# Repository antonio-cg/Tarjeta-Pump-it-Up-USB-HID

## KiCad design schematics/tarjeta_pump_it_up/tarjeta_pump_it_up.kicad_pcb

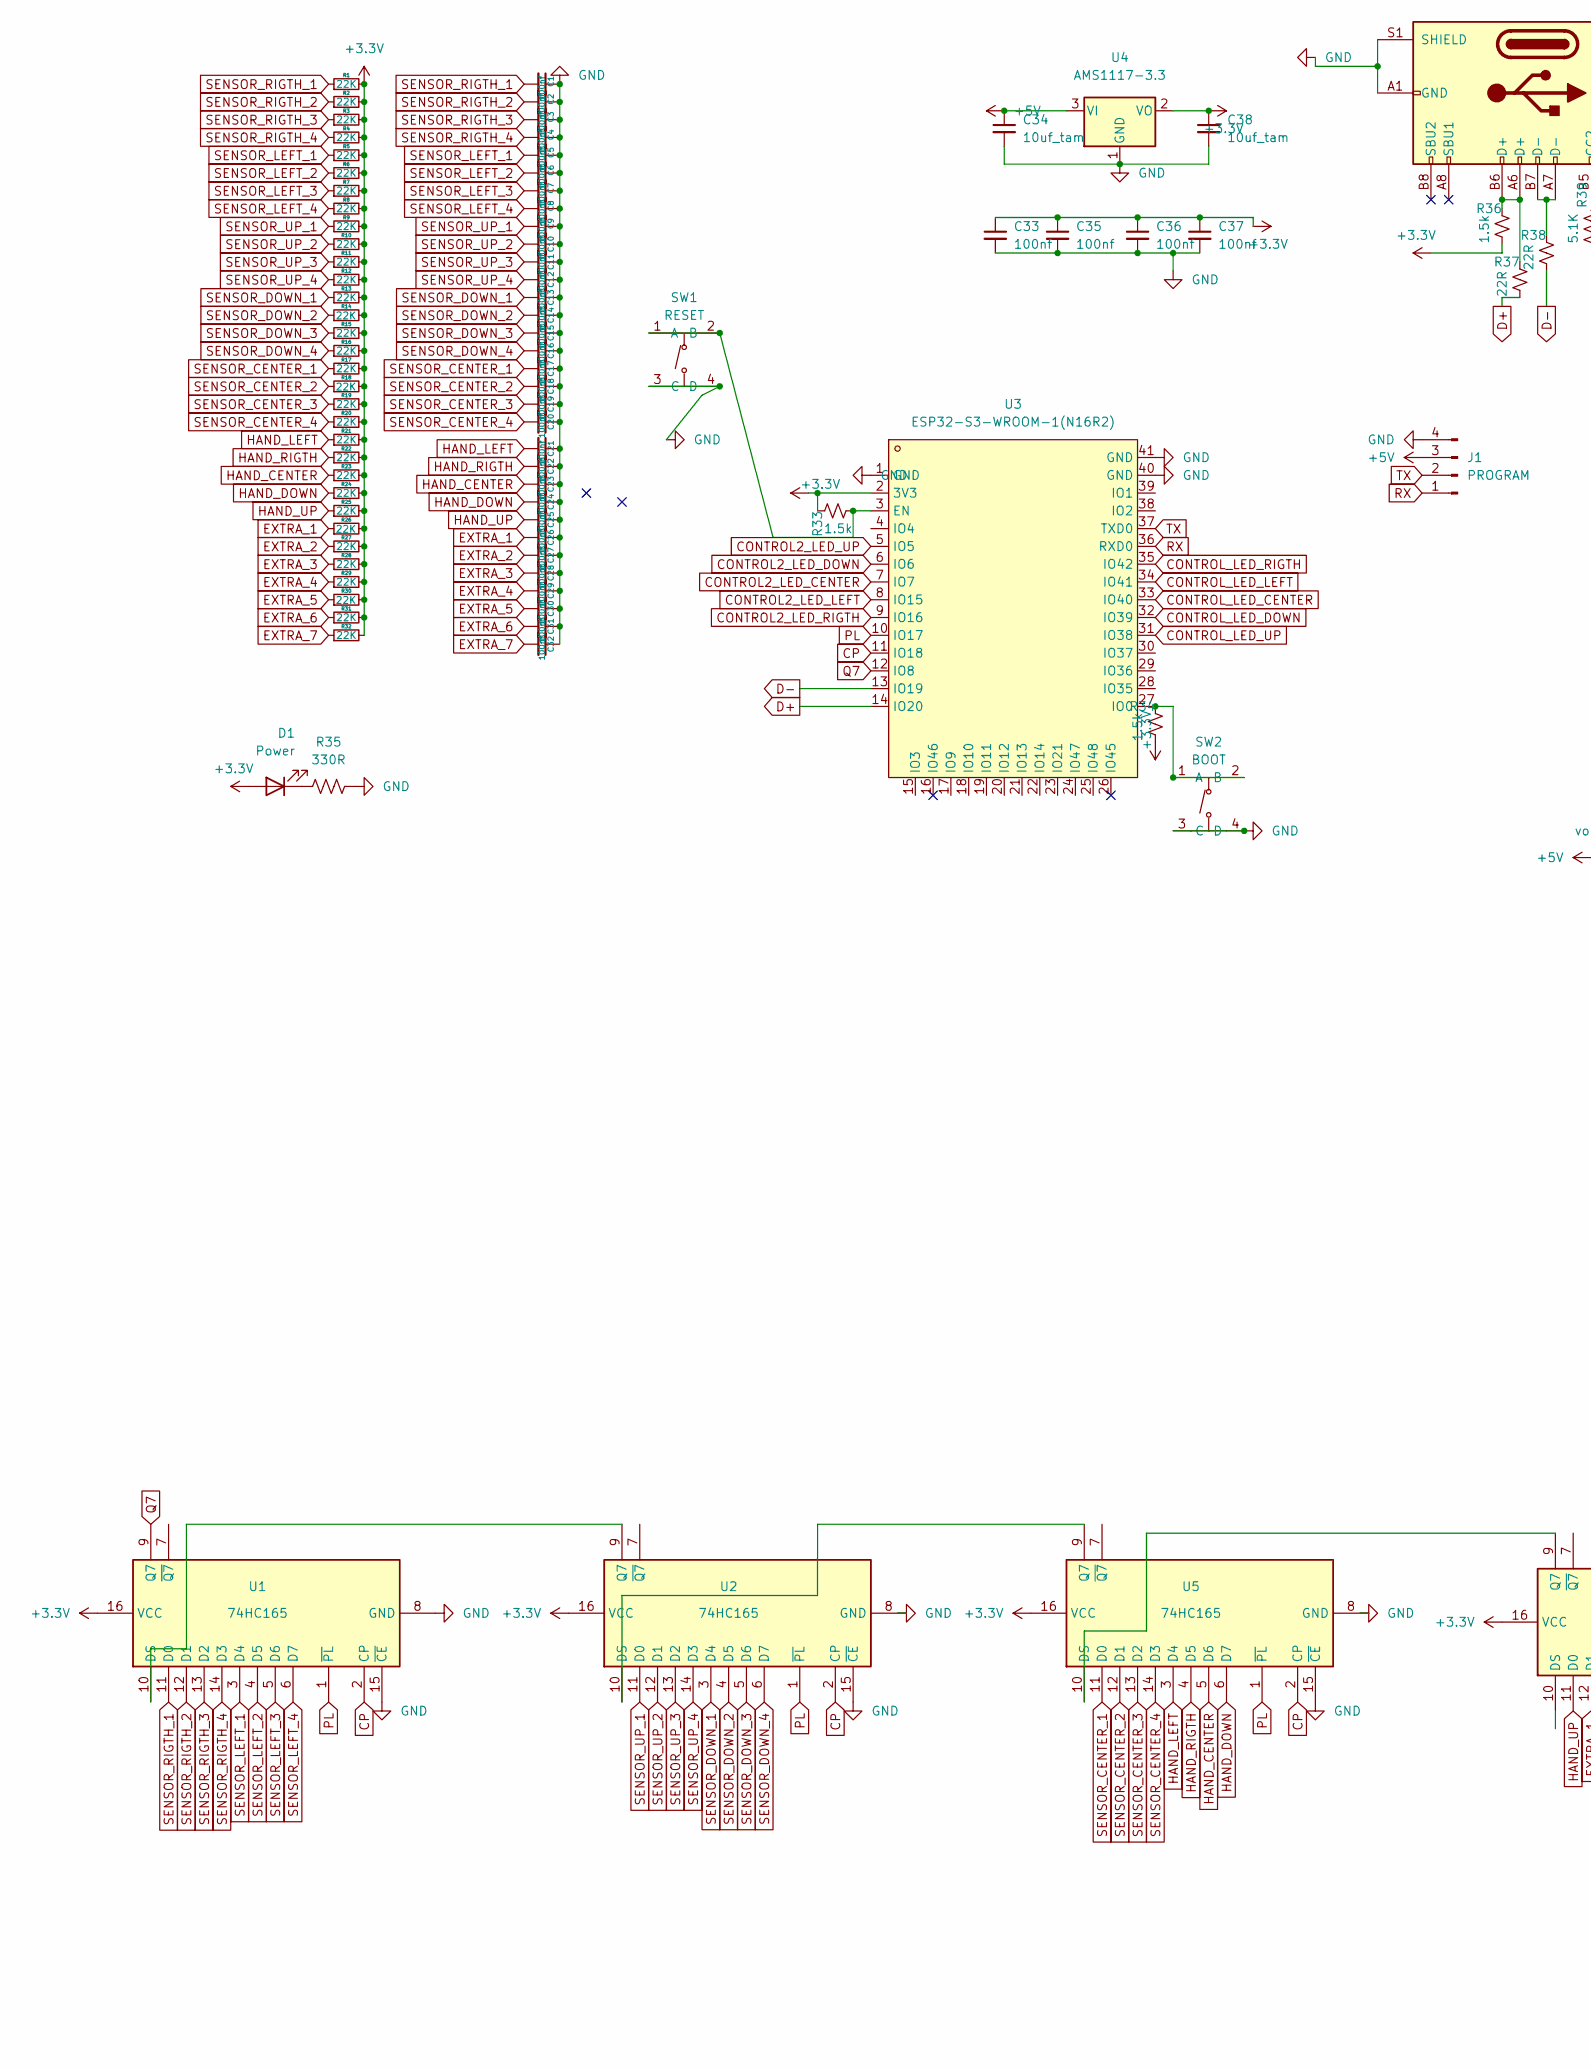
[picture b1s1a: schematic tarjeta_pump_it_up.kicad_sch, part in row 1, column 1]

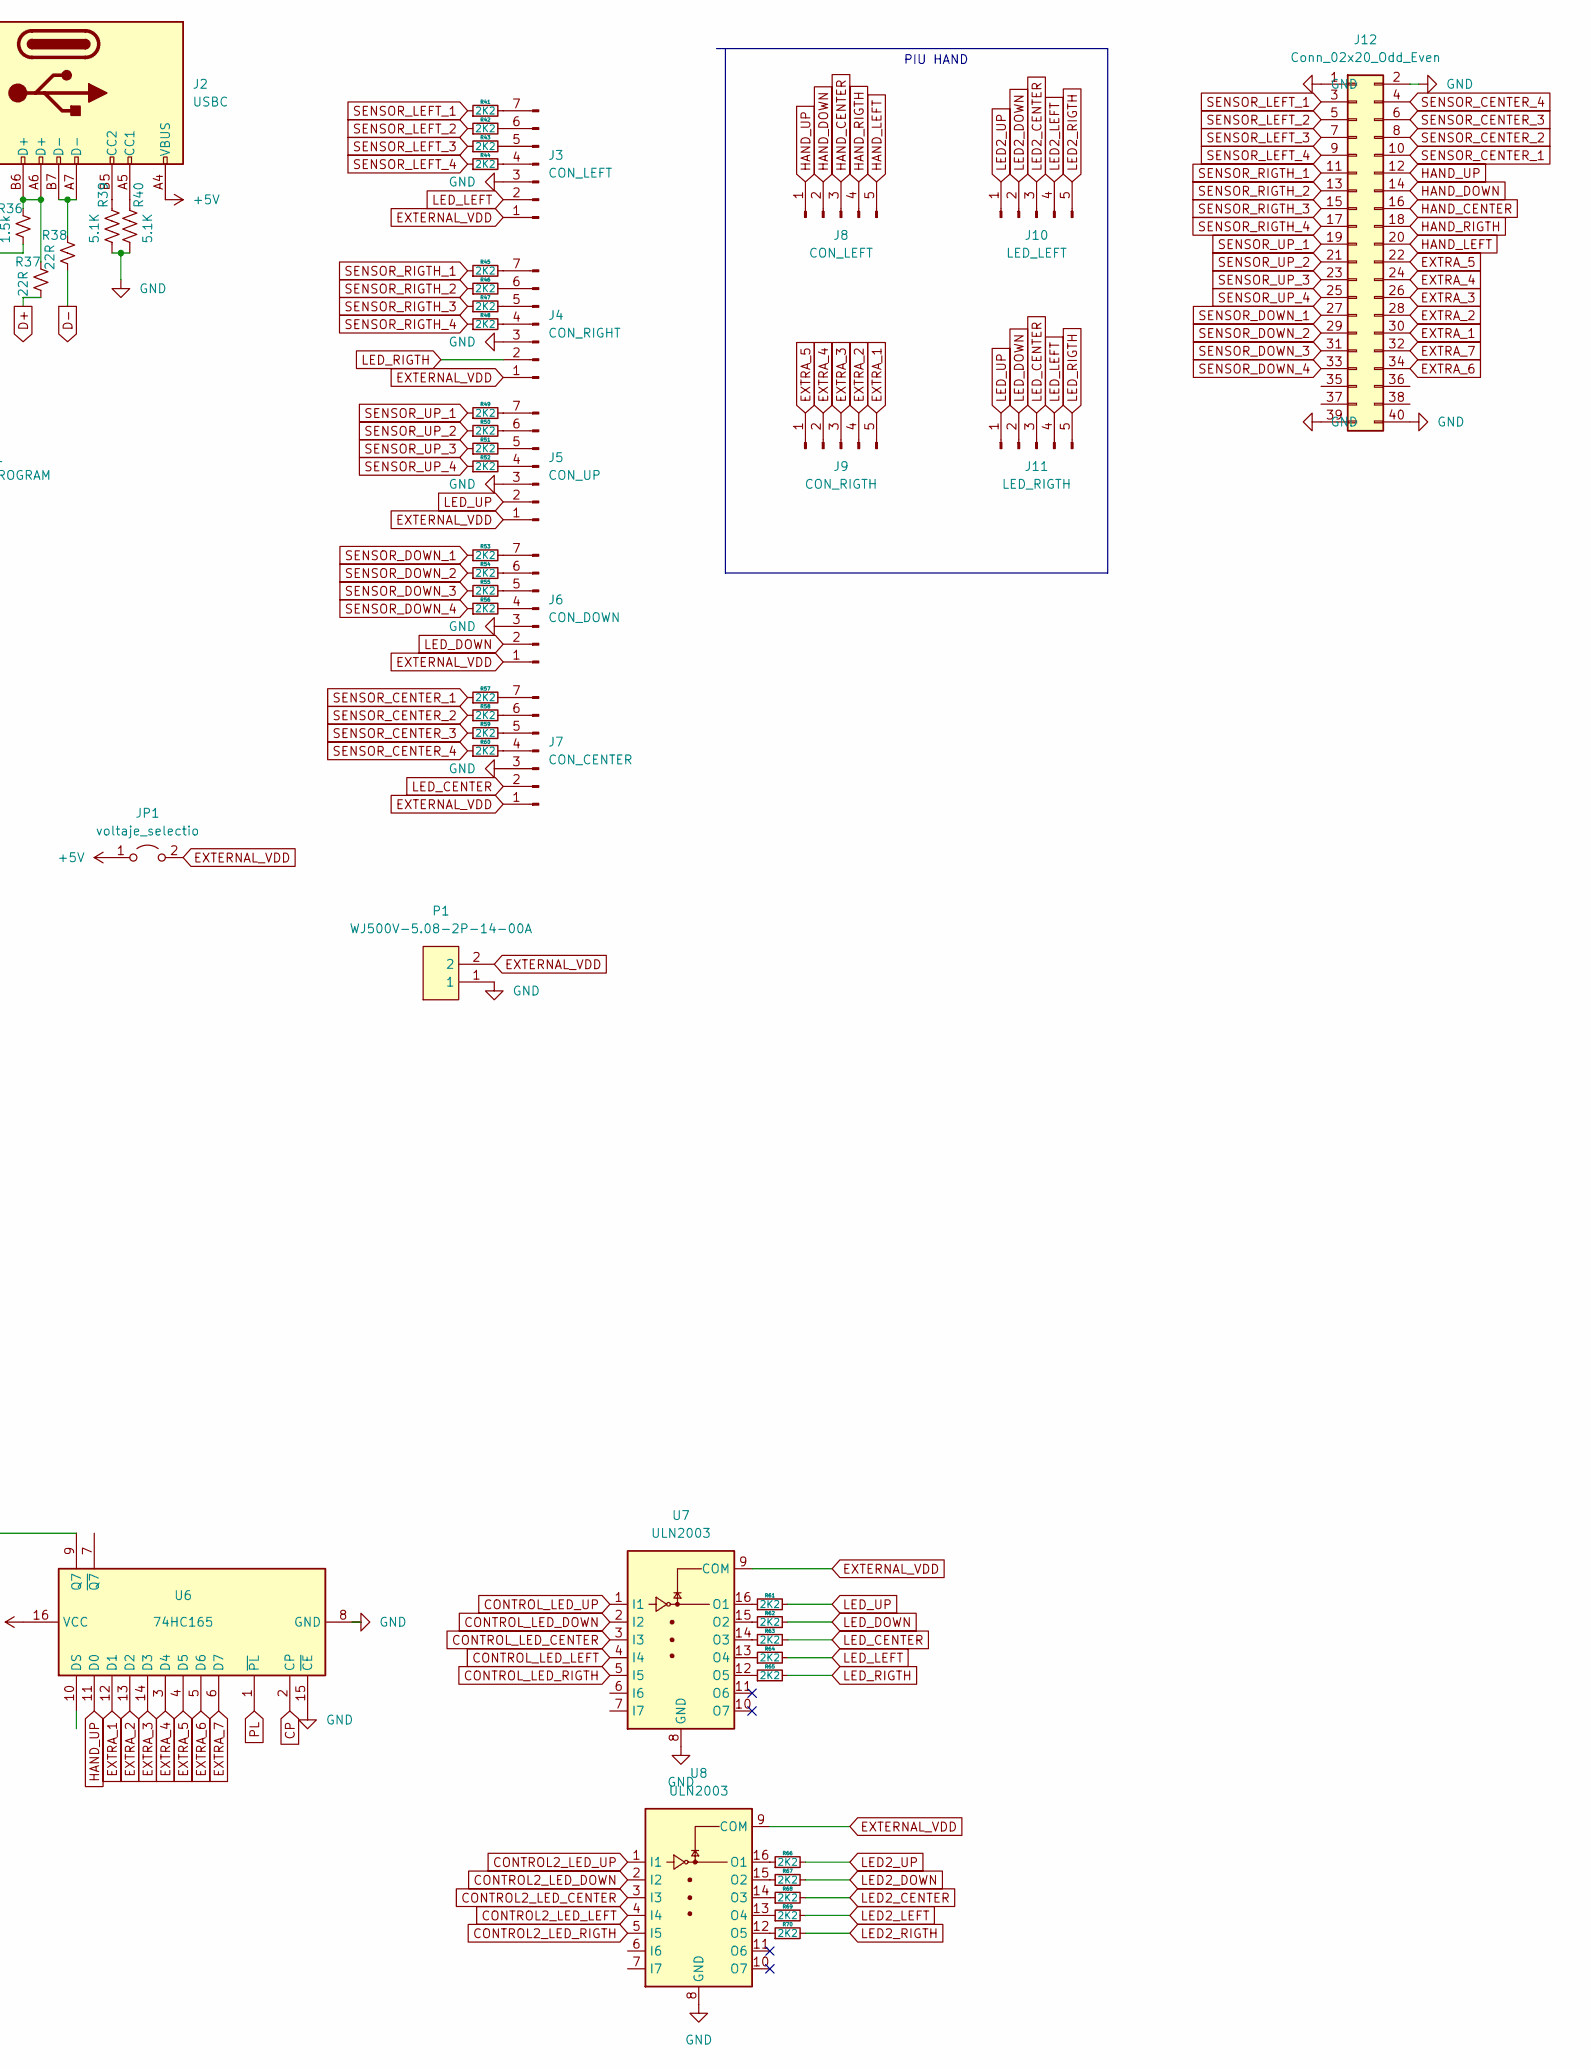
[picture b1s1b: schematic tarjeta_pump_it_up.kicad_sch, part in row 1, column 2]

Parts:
C1, C2, C3, C4, C5, C6, C7, C8, C9, C10, C11, C12, C13, C14, C15, C16, C17, C18, C19, C20, C21, C22, C23, C24, C25, C26, C27, C28, C29, C30, C31, C32: 100nf; C_0603_1608Metric; LCSC C14663
C33, C35, C36, C37: 100nf; C_0805_2012Metric; LCSC C49678
C34, C38: 10uf_tam; CP_EIA-3216-18_Kemet-A; LCSC C122912
D1: Power; LED_0805_2012Metric; LCSC C2296
J1: PROGRAM; PinHeader_1x04_P2.54mm_Vertical
J2: USBC; USB-C_SMD-TYPE-C-31-M-12; LCSC C165948
J3: CON_LEFT; PinHeader_1x07_P2.54mm_Vertical
J4: CON_RIGHT; PinHeader_1x07_P2.54mm_Vertical
J5: CON_UP; PinHeader_1x07_P2.54mm_Vertical
J6: CON_DOWN; PinHeader_1x07_P2.54mm_Vertical
J7: CON_CENTER; PinHeader_1x07_P2.54mm_Vertical
J8: CON_LEFT; PinHeader_1x05_P2.54mm_Vertical
J9: CON_RIGTH; PinHeader_1x05_P2.54mm_Vertical
J10: LED_LEFT; PinHeader_1x05_P2.54mm_Vertical
J11: LED_RIGTH; PinHeader_1x05_P2.54mm_Vertical
J12: Conn_02x20_Odd_Even; PinHeader_2x20_P2.54mm_Vertical
JP1: voltaje_selectio; SolderJumper-2_P1.3mm_Open_Pad1.0x1.5mm
P1: WJ500V-5.08-2P-14-00A; CONN-TH_2P-P5.00_WJ500V-5.08-2P; LCSC Part C8465
R1, R2, R3, R4, R5, R6, R7, R8, R9, R10, R11, R12, R13, R14, R15, R16, R17, R18, R19, R20, R21, R22, R23, R24, R25, R26, R27, R28, R29, R30, R31, R32: 22K; R_0603_1608Metric; LCSC C31850
R33, R34, R36: 1.5k; R_0603_1608Metric; LCSC C4310
R35: 330R; R_0603_1608Metric; LCSC C17630
R37, R38: 22R; R_0603_1608Metric; LCSC C17561
R39, R40: 5.1K; R_0603_1608Metric; LCSC C27834
R41, R42, R43, R44, R45, R46, R47, R48, R49, R50, R51, R52, R53, R54, R55, R56, R57, R58, R59, R60, R61, R62, R63, R64, R65, R66, R67, R68, R69, R70: 2K2; R_0603_1608Metric; LCSC C4190
SW1: RESET; SW-SMD_4P-L5.1-W5.1-P3.70-LS6.5-TL-2; LCSC Part C318884
SW2: BOOT; SW-SMD_4P-L5.1-W5.1-P3.70-LS6.5-TL-2; LCSC Part C318884
U1, U2, U5, U6: 74HC165; SOIC-16_L9.9-W3.9-P1.27-LS6.0-BL; LCSC C5613
U3: ESP32-S3-WROOM-1(N16R2); WIRELM-SMD_ESP32-S3-WROOM-1; LCSC Part C2913205
U4: AMS1117-3.3; SOT-223-3_TabPin2; LCSC C6186
U7, U8: ULN2003; SOIC-16_L9.9-W3.9-P1.27-LS6.0-BL; LCSC C7512

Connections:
+3V3: C33.1, C35.1, C36.1, C37.1, C38.1, D1.2 (A), R1.2, R2.2, R3.2, R4.2, R5.2, R6.2, R7.2, R8.2, R9.2, R10.2, R11.2, R12.2, R13.2, R14.2, R15.2, R16.2, R17.2, R18.2, R19.2, R20.2, R21.2, R22.2, R23.2, R24.2, R25.2, R26.2, R27.2, R28.2, R29.2, R30.2, R31.2, R32.2, R33.1, R34.2, R36.2, U1.16 (VCC), U2.16 (VCC), U3.2 (3V3), U4.2 (VO), U5.16 (VCC), U6.16 (VCC)
+5V: C34.1, J1.3, J2.A4 (VBUS), J2.A9 (VBUS), J2.B4 (VBUS), J2.B9 (VBUS), JP1.1 (A), U4.3 (VI)
CONTROL2_LED_CENTER: U3.7 (IO7), U8.3 (I3)
CONTROL2_LED_DOWN: U3.6 (IO6), U8.2 (I2)
CONTROL2_LED_LEFT: U3.8 (IO15), U8.4 (I4)
CONTROL2_LED_RIGTH: U3.9 (IO16), U8.5 (I5)
CONTROL2_LED_UP: U3.5 (IO5), U8.1 (I1)
CONTROL_LED_CENTER: U3.33 (IO40), U7.3 (I3)
CONTROL_LED_DOWN: U3.32 (IO39), U7.2 (I2)
CONTROL_LED_LEFT: U3.34 (IO41), U7.4 (I4)
CONTROL_LED_RIGTH: U3.35 (IO42), U7.5 (I5)
CONTROL_LED_UP: U3.31 (IO38), U7.1 (I1)
CP: U1.2 (CP), U2.2 (CP), U3.11 (IO18), U5.2 (CP), U6.2 (CP)
D+: R37.2, U3.14 (IO20)
D-: R38.2, U3.13 (IO19)
EXTERNAL_VDD: J3.1, J4.1, J5.1, J6.1, J7.1, JP1.2 (B), P1.2, U7.9 (COM), U8.9 (COM)
EXTRA_1: C26.2, J9.5, J12.30, R26.1, U6.12 (D1)
EXTRA_2: C27.2, J9.4, J12.28, R27.1, U6.13 (D2)
EXTRA_3: C28.2, J9.3, J12.26, R28.1, U6.14 (D3)
EXTRA_4: C29.2, J9.2, J12.24, R29.1, U6.3 (D4)
EXTRA_5: C30.2, J9.1, J12.22, R30.1, U6.4 (D5)
EXTRA_6: C31.2, J12.34, R31.1, U6.5 (D6)
EXTRA_7: C32.2, J12.32, R32.1, U6.6 (D7)
GND: C1.1, C2.1, C3.1, C4.1, C5.1, C6.1, C7.1, C8.1, C9.1, C10.1, C11.1, C12.1, C13.1, C14.1, C15.1, C16.1, C17.1, C18.1, C19.1, C20.1, C21.1, C22.1, C23.1, C24.1, C25.1, C26.1, C27.1, C28.1, C29.1, C30.1, C31.1, C32.1, C33.2, C34.2, C35.2, C36.2, C37.2, C38.2, J1.4, J2.A1 (GND), J2.A12 (GND), J2.B1 (GND), J2.B12 (GND), J2.S1 (SHIELD), J3.3, J4.3, J5.3, J6.3, J7.3, J12.1, J12.2, J12.39, J12.40, P1.1, R35.2, R39.1, R40.1, SW1.3 (C), SW1.4 (D), SW2.3 (C), SW2.4 (D), U1.8 (GND), U1.15 (~CE), U2.8 (GND), U2.15 (~CE), U3.1 (GND), U3.40 (GND), U3.41 (GND), U4.1 (GND), U5.8 (GND), U5.15 (~CE), U6.8 (GND), U6.15 (~CE), U7.8 (GND), U8.8 (GND)
HAND_CENTER: C23.2, J8.3, J12.16, R23.1, U5.5 (D6)
HAND_DOWN: C24.2, J8.2, J12.14, R24.1, U5.6 (D7)
HAND_LEFT: C21.2, J8.5, J12.20, R21.1, U5.3 (D4)
HAND_RIGTH: C22.2, J8.4, J12.18, R22.1, U5.4 (D5)
HAND_UP: C25.2, J8.1, J12.12, R25.1, U6.11 (D0)
LED2_CENTER: J10.3, R68.2
LED2_DOWN: J10.2, R67.2
LED2_LEFT: J10.4, R69.2
LED2_RIGTH: J10.5, R70.2
LED2_UP: J10.1, R66.2
LED_CENTER: J7.2, J11.3, R63.2
LED_DOWN: J6.2, J11.2, R62.2
LED_LEFT: J3.2, J11.4, R64.2
LED_RIGTH: J4.2, J11.5, R65.2
LED_UP: J5.2, J11.1, R61.2
unnamed: D1.1 (K), R35.1
unnamed: J2.A5 (CC1), R40.2
unnamed: J2.A6 (D+), J2.B6 (D+), R36.1, R37.1
unnamed: J2.A7 (D-), J2.B7 (D-), R38.1
unnamed: J2.B5 (CC2), R39.2
unnamed: J3.4, R44.2
unnamed: J3.5, R43.2
unnamed: J3.6, R42.2
unnamed: J3.7, R41.2
unnamed: J4.4, R48.2
unnamed: J4.5, R47.2
unnamed: J4.6, R46.2
unnamed: J4.7, R45.2
unnamed: J5.4, R52.2
unnamed: J5.5, R51.2
unnamed: J5.6, R50.2
unnamed: J5.7, R49.2
unnamed: J6.4, R56.2
unnamed: J6.5, R55.2
unnamed: J6.6, R54.2
unnamed: J6.7, R53.2
unnamed: J7.4, R60.2
unnamed: J7.5, R59.2
unnamed: J7.6, R58.2
unnamed: J7.7, R57.2
unnamed: R33.2, SW1.1 (A), SW1.2 (B), U3.3 (EN)
unnamed: R34.1, SW2.1 (A), SW2.2 (B), U3.27 (IO0)
unnamed: R61.1, U7.16 (O1)
unnamed: R62.1, U7.15 (O2)
unnamed: R63.1, U7.14 (O3)
unnamed: R64.1, U7.13 (O4)
unnamed: R65.1, U7.12 (O5)
unnamed: R66.1, U8.16 (O1)
unnamed: R67.1, U8.15 (O2)
unnamed: R68.1, U8.14 (O3)
unnamed: R69.1, U8.13 (O4)
unnamed: R70.1, U8.12 (O5)
unnamed: U1.10 (DS), U2.9 (Q7)
unnamed: U2.10 (DS), U5.9 (Q7)
unnamed: U5.10 (DS), U6.9 (Q7)
PL: U1.1 (~PL), U2.1 (~PL), U3.10 (IO17), U5.1 (~PL), U6.1 (~PL)
Q7: U1.9 (Q7), U3.12 (IO8)
RX: J1.1, U3.36 (RXD0)
SENSOR_CENTER_1: C17.2, J12.10, R17.1, R57.1, U5.11 (D0)
SENSOR_CENTER_2: C18.2, J12.8, R18.1, R58.1, U5.12 (D1)
SENSOR_CENTER_3: C19.2, J12.6, R19.1, R59.1, U5.13 (D2)
SENSOR_CENTER_4: C20.2, J12.4, R20.1, R60.1, U5.14 (D3)
SENSOR_DOWN_1: C13.2, J12.27, R13.1, R53.1, U2.3 (D4)
SENSOR_DOWN_2: C14.2, J12.29, R14.1, R54.1, U2.4 (D5)
SENSOR_DOWN_3: C15.2, J12.31, R15.1, R55.1, U2.5 (D6)
SENSOR_DOWN_4: C16.2, J12.33, R16.1, R56.1, U2.6 (D7)
SENSOR_LEFT_1: C5.2, J12.3, R5.1, R41.1, U1.3 (D4)
SENSOR_LEFT_2: C6.2, J12.5, R6.1, R42.1, U1.4 (D5)
SENSOR_LEFT_3: C7.2, J12.7, R7.1, R43.1, U1.5 (D6)
SENSOR_LEFT_4: C8.2, J12.9, R8.1, R44.1, U1.6 (D7)
SENSOR_RIGTH_1: C1.2, J12.11, R1.1, R45.1, U1.11 (D0)
SENSOR_RIGTH_2: C2.2, J12.13, R2.1, R46.1, U1.12 (D1)
SENSOR_RIGTH_3: C3.2, J12.15, R3.1, R47.1, U1.13 (D2)
SENSOR_RIGTH_4: C4.2, J12.17, R4.1, R48.1, U1.14 (D3)
SENSOR_UP_1: C9.2, J12.19, R9.1, R49.1, U2.11 (D0)
SENSOR_UP_2: C10.2, J12.21, R10.1, R50.1, U2.12 (D1)
SENSOR_UP_3: C11.2, J12.23, R11.1, R51.1, U2.13 (D2)
SENSOR_UP_4: C12.2, J12.25, R12.1, R52.1, U2.14 (D3)
TX: J1.2, U3.37 (TXD0)

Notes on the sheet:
PIU HAND

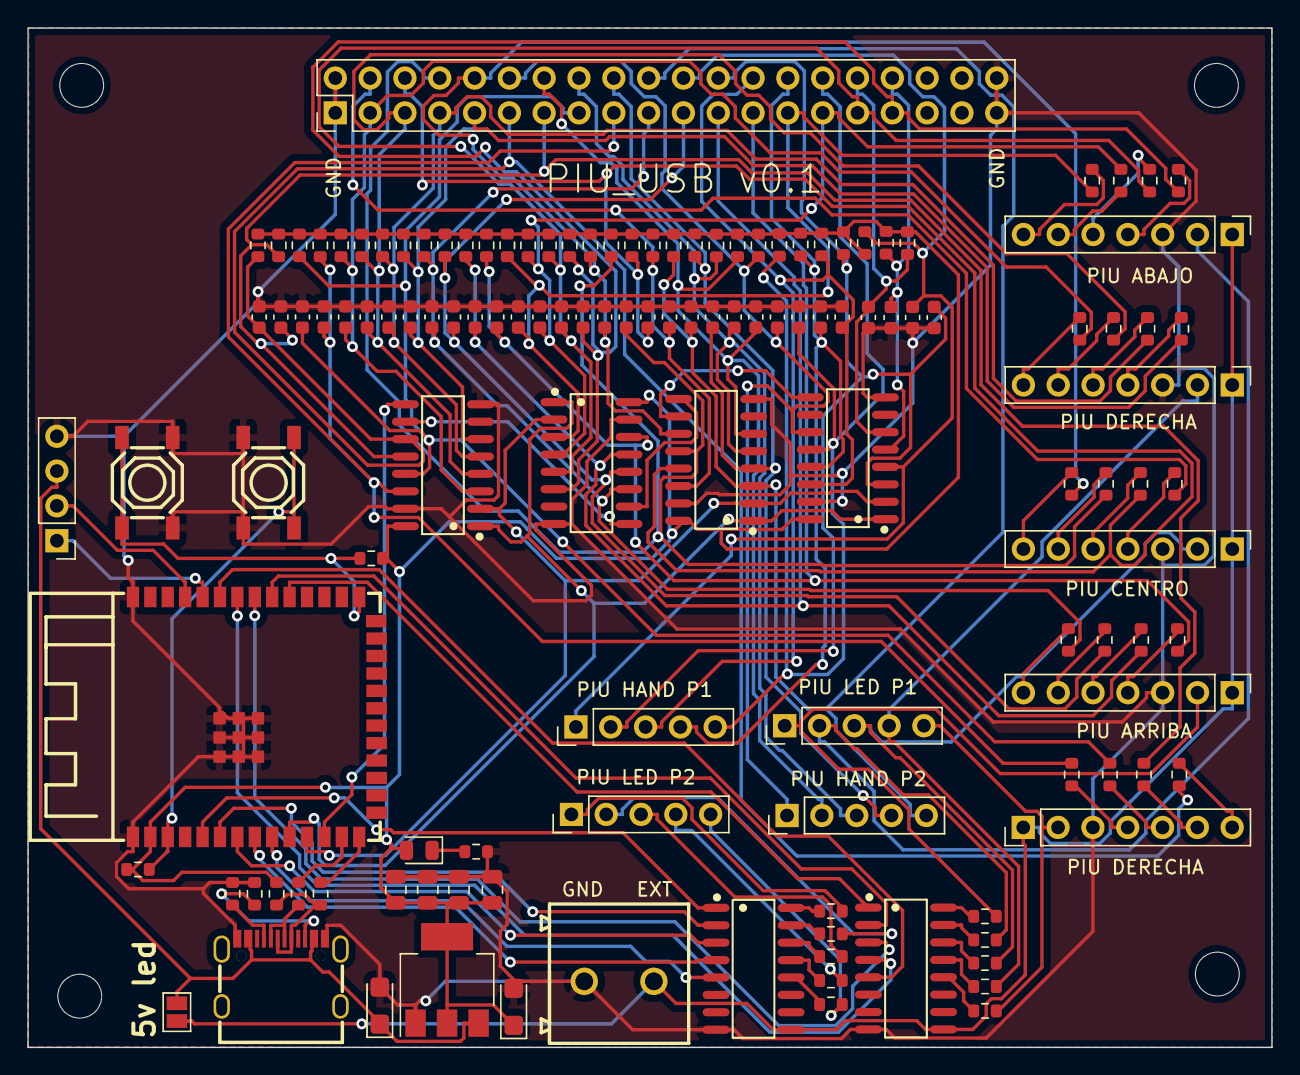
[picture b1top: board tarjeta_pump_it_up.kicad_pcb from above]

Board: 2 copper layers, 90.8 x 74.4 mm, 137 parts (0 on the bottom side), 103 nets.

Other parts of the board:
REF2: MountingHole_3.2mm_M3
m1, m2, m3: MountingHole_3.2mm_M3

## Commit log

2025-09-10 primera version
    primera version mandada para produccion
